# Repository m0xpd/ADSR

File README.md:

# ADSR
A Looping Version of the YuSynth ADSR

# Background

I decided to build a new envelope generator back in December 2022 to supplement / replace my old AR generators made from [MFOS](http://musicfromouterspace.com/) designs and my 
own ["ADSRduino"](https://github.com/m0xpd/ADSRduino).

I already knew Yves Usson's excellent [YuSynth site](https://yusynth.net/Modular/index_en.html) (having published a Eurorack version of the ['Simple VCA'](https://github.com/m0xpd/YuSynth-VCA-for-Eurorack)), and was interested by a comment on 
[Eddy Bergman's website](https://www.eddybergman.com/2020/03/synthesizer-build-part-24-adsr-with.html) about the YuSynth ADSR.

Eddy said:

> "I can say without any doubt that this design is perfect if you want a good and reliable ADSR to pair with your VCA or to drive a filter. " 

That settled it - I would make a Eurorack version of Yves' 7555-based design. However, having added looping to my ADSRduino, 
I decided that I would also like to include the same looping functionality on the new envelope generator. 

So - here it is. A version of the YuSynth 7555 ADSR in 8HP with looping...

<p width=100%, align="center">
 &nbsp &nbsp &nbsp &nbsp &nbsp &nbsp &nbsp &nbsp 
</p>

# Circuit Details

The schematic is seen below (click for a full-sized version and/or download from the 'images' folder).

You will see that I follow Yves' original schematic pretty closely, apart from the addition of the elements required to realise the 
looping functionality. These are:
* a comparator (IC1B) to detect when the envelope falls below the PN junction drop (over D5)
* a positive edge detector (R24/C4/D6) to get a trigger when the envelope falls below the PN junction drop and
* a one-shot monostable multivibrator (Q5,6 etc), to generate a defined pulse from this trigger, 

which is applied via D7 back to the input stage. If the looping switch (SW2) is set appropriately, this pulse can re-trigger the 
envelope and cause 'looping'.

The old-school transistor one-shot is included because I didn't want to add another IC package (having already 'spent' the last stage 
of IC1 on the comparator task).

Other minor departures from Yves' "words and music" include a reduction in input resistor R6 (I had trouble with the specified 1M) and 
substitution of a 2N7000 for Yves' specified BS170 (I see others have had difficuty sourcing these rarer FETs and the garden-variety 
2N7000 works fine). 

I also chose to use once again the lovely [low-profile push button](https://www.thonk.co.uk/shop/low-profile-led-buttons/) as both 
manual gate switch and indicator. It is the right height to work with [Thonkiconns](https://www.thonk.co.uk/shop/thonkiconn/) and [Alpha pots](https://www.thonk.co.uk/shop/alpha-9mm-pots-vertical-t18/), which makes mechanical assembly a breeze.

# Construction Details

Full details of the PCB are given in the [PCB folder](PCB), which includes a .sch and .brd file, developed in EAGLE.

A front panel is decribed by a Kicad project in the [Front Panel folder.](Front%20Panel)

My original boards and Front panel (seen in the images above) were made by JLC, who did their usual competent job. 

The images show the v0.1 boards, which include a Molex KK connector for power which is not on the present V2.0 design. They also have 
different silkscreening, influencing most significantly the licensing...

# Licensing

Yves is clear on the position with copyright on his website:

> "All circuits, schematics, printed circuit board, panel design and associated data published on (yusynth.net) can be used for private use only." 

and:

> "The projects of (yusynth.net) may be build for personal, private usage or educative purpose. Commercial exploitation of the schematics, circuits, 
front panels and software shown on (yusynth.net), is not permitted without a formal agreement with (Yves Usson)".

Accordingly, **the copyright for the core of this ADSR circuit rests with Yves and no commercial exploitation is permitted**.

I have reflected this in the [License](LICENSE.txt) for the looping Eurorack version presented in this repository.

This work is licensed under a
[Creative Commons Attribution-NonCommercial-ShareAlike 4.0 International License.](https://creativecommons.org/licenses/by-nc-sa/4.0/deed.en)

# Specifications

The looping ADSR is 8HP wide and extends 25mm behind the front panel.

It consumes:

7.1mA from the 12V rail (max current in looping mode; quiescent current drain is 3.7mA)  

1.1mA from the -12V rail (in all conditions) 

nothing from the 5V rail.

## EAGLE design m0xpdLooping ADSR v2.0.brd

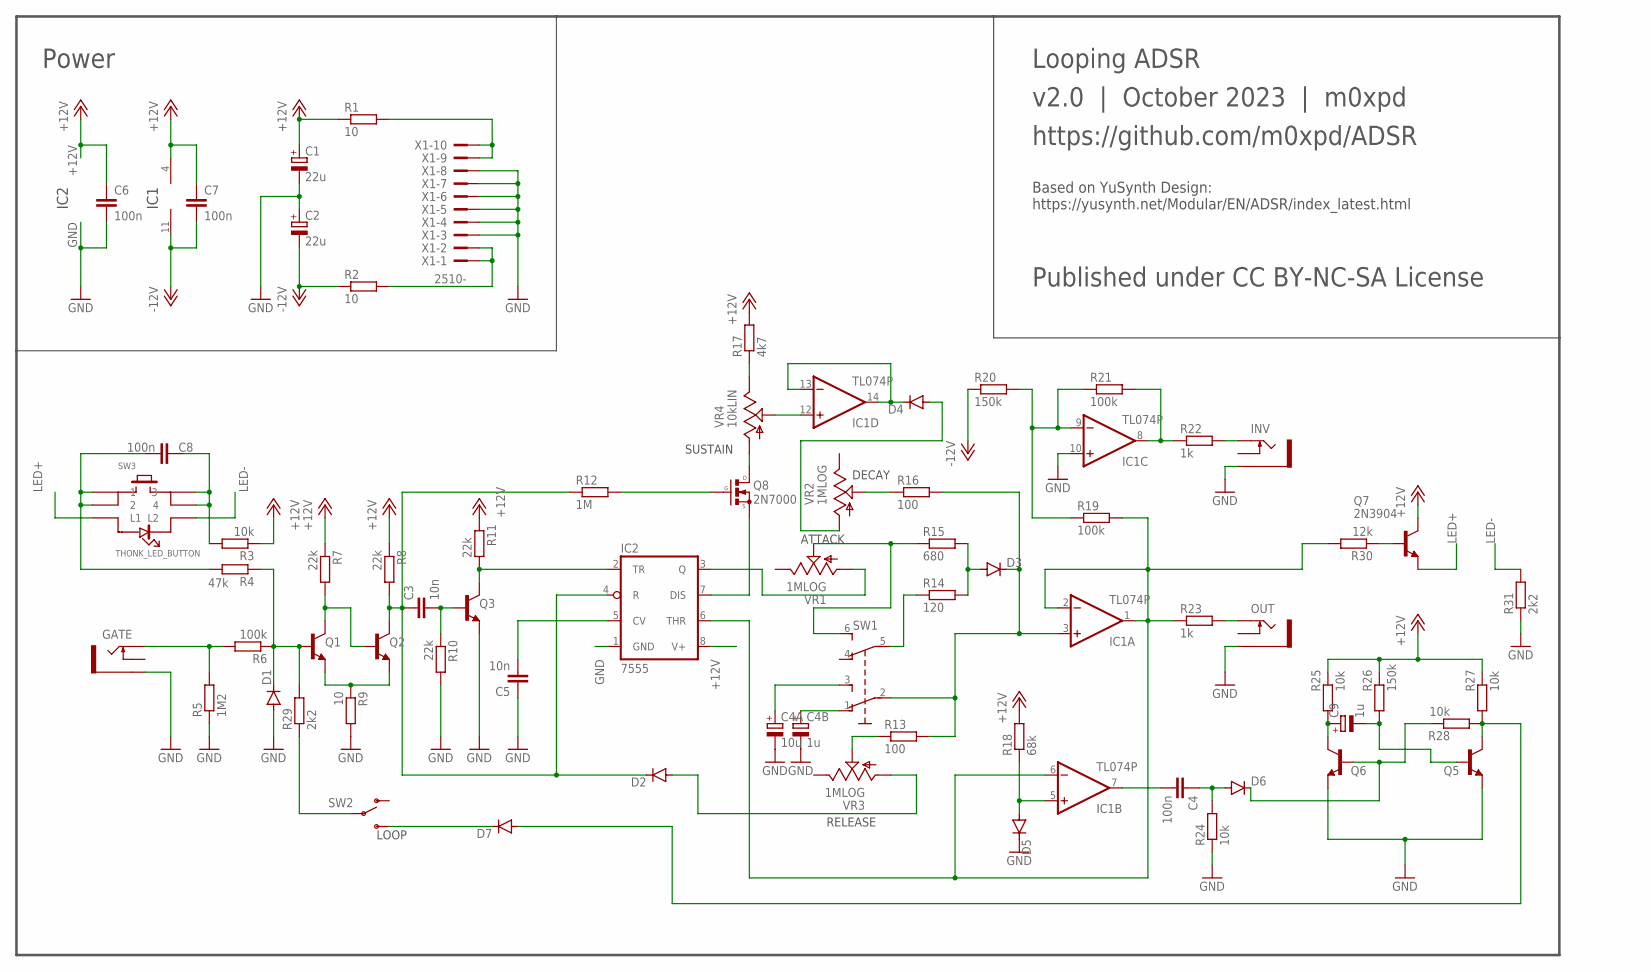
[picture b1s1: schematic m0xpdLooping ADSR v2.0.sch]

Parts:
C1, C2: 22u; E2,5-5
C3, C5: 10n; C050-025X075
C4, C6, C7: 100n; C050-025X075
C4A: 10u; E2,5-5
C4B, C9: 1u; E2,5-5
C8: 100n; C025-030X050
D1, D2, D3, D4, D5, D6, D7: 1N4148DO35-7; DO35-7
GATE: THONKICONNNEW; WQP-PJ301M-12_JACK
IC1: TL074P; DIL14
IC2: 7555; DIL08
INV: THONKICONNNEW; WQP-PJ301M-12_JACK
OUT: THONKICONNNEW; WQP-PJ301M-12_JACK
Q1, Q2, Q3, Q5, Q6, Q7: 2N3904; TO92
Q8: 2N7000; TO92
R1, R2, R9: 10; 0204/7
R3, R24, R25, R27, R28: 10k; 0204/7
R4: 47k; 0204/7
R5: 1M2; 0204/7
R6, R19, R21: 100k; 0204/7
R7, R8, R10, R11: 22k; 0204/7
R12: 1M; 0204/7
R13, R16: 100; 0204/7
R14: 120; 0204/7
R15: 680; 0204/7
R17: 4k7; 0204/7
R18: 68k; 0204/7
R20, R26: 150k; 0204/7
R22, R23: 1k; 0204/7
R29, R31: 2k2; 0204/7
R30: 12k; 0204/7
SW1: TL46PO; TL4XPO
SW2: SUBMINI_SPDT; SUBMINI_TOGGLE
SW3: THONK_LED_BUTTON; LOW_PROFILE_BUTTON
VR1, VR2, VR3: 1MLOG; 9MM_SNAP-IN_POT
VR4: 10kLIN; 9MM_SNAP-IN_POT
X1: 2510-; PAK100/2500-10

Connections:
+12V: C1.+, C6.1, C7.1, IC1.4 (V+), IC2.8 (V+), Q7.1 (C), R1.1, R3.1, R7.1, R8.1, R11.1, R17.2, R18.2, R25.2, R26.2, R27.2
-12V: C2.-, C7.2, IC1.11 (V-), R2.1, R20.1
GND: C1.-, C2.+, C4A.-, C4B.-, C5.1, C6.2, D1.A, D5.C, GATE.P$3_SLEEVE (SLEEVE), IC1.10 (+IN), IC2.1 (GND), INV.P$3_SLEEVE (SLEEVE), OUT.P$3_SLEEVE (SLEEVE), Q3.3 (E), Q5.3 (E), Q6.3 (E), R5.1, R9.2, R10.2, R24.1, R31.1, X1.3, X1.4, X1.5, X1.6, X1.7, X1.8
LED+: Q7.3 (E), SW3.L$1 (L1)
LED-: R31.2, SW3.L$2 (L2)
unnamed: R1.2, X1.9, X1.10
unnamed: GATE.P$1_TIP (TIP), R5.2, R6.2
unnamed: D1.C, Q1.2 (B), R4.1, R6.1, R29.2
unnamed: Q1.3 (E), Q2.3 (E), R9.1
unnamed: R2.2, X1.1, X1.2
unnamed: IC2.3 (Q), VR1.1 (A)
unnamed: Q1.1 (C), Q2.2 (B), R7.2
unnamed: C3.2, Q3.2 (B), R10.1
unnamed: IC2.2 (TR), Q3.1 (C), R11.2
unnamed: C5.2, IC2.5 (CV)
unnamed: C3.1, D2.C, IC2.4 (R), Q2.1 (C), R8.2, R12.1
unnamed: Q8.2 (G), R12.2
unnamed: IC2.7 (DIS), Q8.1 (S)
unnamed: D2.A, VR3.1 (A)
unnamed: Q8.3 (D), VR4.1 (A)
unnamed: R17.1, VR4.3 (E)
unnamed: R13.1, VR3.2 (S)
unnamed: R15.1, SW1.6 (S1), VR1.2 (S)
unnamed: R14.1, SW1.5 (P1)
unnamed: D3.A, R14.2, R15.2
unnamed: D3.C, IC1.3 (+IN), R13.2, R16.2, SW1.2
unnamed: R16.1, VR2.2 (S)
unnamed: C4A.+, SW1.3 (S)
unnamed: C4B.+, SW1.1 (O)
unnamed: IC1.1 (OUT), IC1.2 (-IN), IC1.6 (-IN), IC2.6 (THR), R19.2, R23.1, R30.2
unnamed: IC1.12 (+IN), VR4.2 (S)
unnamed: D4.C, IC1.13 (-IN), IC1.14 (OUT)
unnamed: D4.A, VR2.1 (A)
unnamed: D5.A, IC1.5 (+IN), R18.1
unnamed: IC1.9 (-IN), R19.1, R20.2, R21.1
unnamed: C4.2, IC1.7 (OUT)
unnamed: IC1.8 (OUT), R21.2, R22.1
unnamed: INV.P$1_TIP (TIP), R22.2
unnamed: OUT.P$1_TIP (TIP), R23.2
unnamed: C8.1, R3.2, SW3.P$3 (3), SW3.P$4 (4)
unnamed: C8.2, R4.2, SW3.P$1 (1), SW3.P$2 (2)
unnamed: C4.1, D6.A, R24.2
unnamed: D7.A, Q5.1 (C), R27.1, R28.1
unnamed: C9.+, Q6.1 (C), R25.1
unnamed: R29.1, SW2.COM (COMMON)
unnamed: C9.-, Q5.2 (B), R26.1
unnamed: D7.C, SW2.3 (S)
unnamed: D6.C, Q6.2 (B), R28.2
unnamed: Q7.2 (B), R30.1

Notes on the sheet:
SUSTAIN
DECAY
ATTACK
RELEASE
Looping ADSR
Based on YuSynth Design: https://yusynth.net/Modular/EN/ADSR/index_latest.html
v2.0 | October 2023 | m0xpd
https://github.com/m0xpd/ADSR
Published under CC BY-NC-SA License
LOOP
Power
IC1
IC2

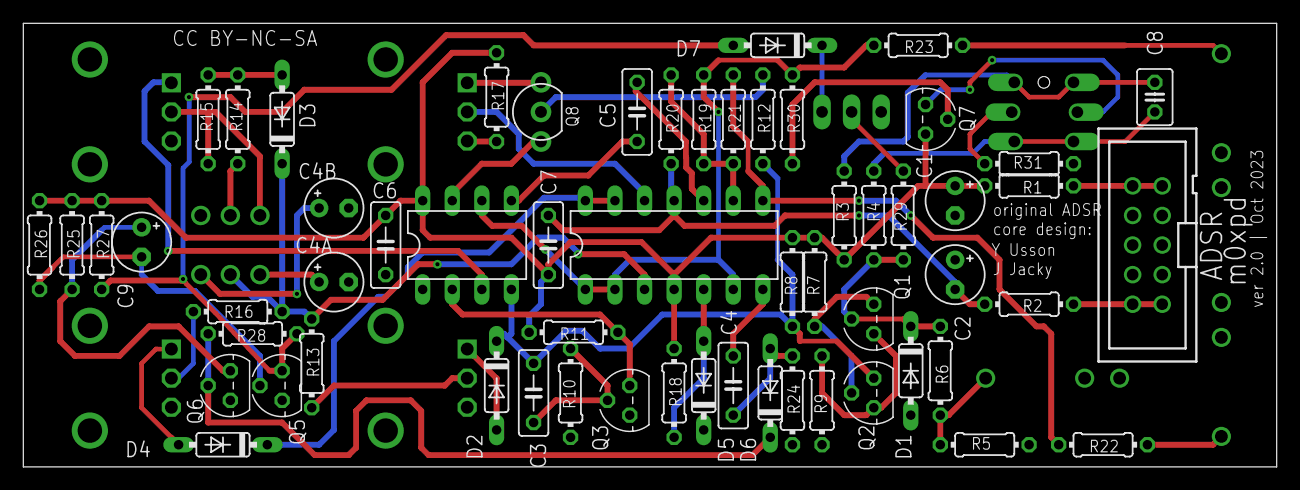
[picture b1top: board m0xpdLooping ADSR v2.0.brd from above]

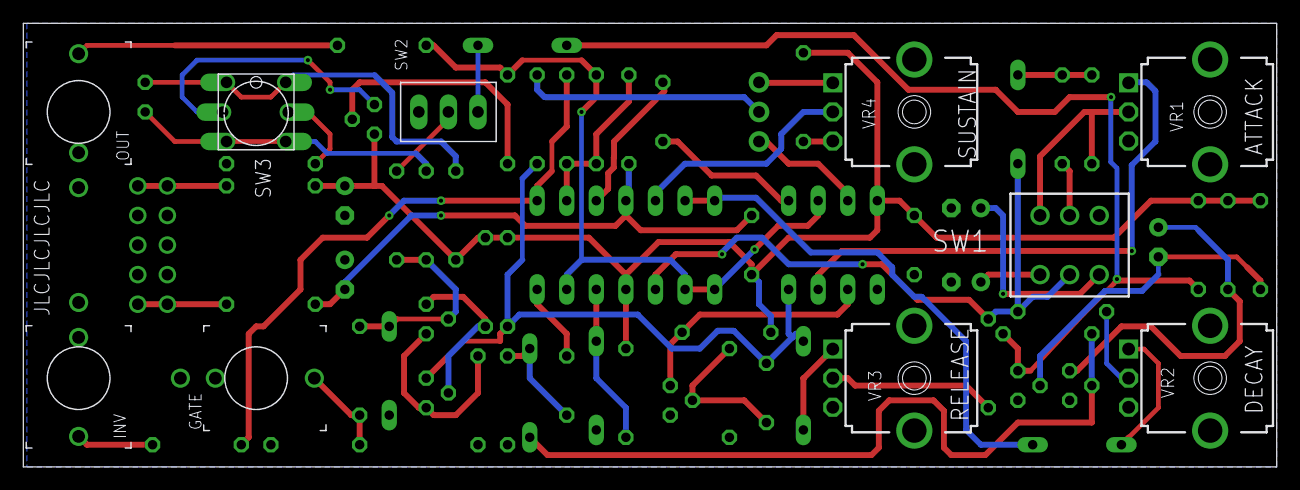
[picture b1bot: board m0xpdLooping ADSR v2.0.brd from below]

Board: 2 copper layers, 107.6 x 38.1 mm, 69 parts (10 on the bottom side), 49 nets.

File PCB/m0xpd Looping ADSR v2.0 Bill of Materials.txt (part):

Partlist exported from /Users/pauldarlington/Documents/EAGLE/projects/555 ADSR/m0xpdLooping ADSR v2.0.sch at 15/10/2023 13:20

Part Value            Device           Package            Description                                                       MF MPN         OC_FARNELL OC_NEWARK POPULARITY SPICEPREFIX
C1   22u              CPOL-EUE2.5-5    E2,5-5             POLARIZED CAPACITOR, European symbol                                                                  16         C          
C2   22u              CPOL-EUE2.5-5    E2,5-5             POLARIZED CAPACITOR, European symbol                                                                  16         C          
C3   10n              C-EU050-025X075  C050-025X075       CAPACITOR, European symbol                                                                            29         C          
C4   100n             C-EU050-025X075  C050-025X075       CAPACITOR, European symbol                                                                            29         C          
C4A  10u              CPOL-EUE2.5-5    E2,5-5             POLARIZED CAPACITOR, European symbol                                                                  16         C          
C4B  1u               CPOL-EUE2.5-5    E2,5-5             POLARIZED CAPACITOR, European symbol                                                                  16         C          
C5   10n              C-EU050-025X075  C050-025X075       CAPACITOR, European symbol                                                                            29         C          
C6   100n             C-EU050-025X075  C050-025X075       CAPACITOR, European symbol                                                                            29         C          
C7   100n             C-EU050-025X075  C050-025X075       CAPACITOR, European symbol                                                                            29         C          
C8   100n             C-EU025-030X050  C025-030X050       CAPACITOR, European symbol                                                                            14         C          
C9   1u               CPOL-EUE2.5-5    E2,5-5             POLARIZED CAPACITOR, European symbol                                                                  16         C          
D1   1N4148DO35-7     1N4148DO35-7     DO35-7             DIODE                                                                                                 58                    
D2   1N4148DO35-7     1N4148DO35-7     DO35-7             DIODE                                                                                                 58                    
D3   1N4148DO35-7     1N4148DO35-7     DO35-7             DIODE                                                                                                 58                    
D4   1N4148DO35-7     1N4148DO35-7     DO35-7             DIODE                                                                                                 58                    
D5   1N4148DO35-7     1N4148DO35-7     DO35-7             DIODE                                                                                                 58                    
D6   1N4148DO35-7     1N4148DO35-7     DO35-7             DIODE                                                                                                 58                    
D7   1N4148DO35-7     1N4148DO35-7     DO35-7             DIODE                                                                                                 58                    
GATE THONKICONNNEW    THONKICONNNEW    WQP-PJ301M-12_JACK 3.5mm socket for Eurorack modular synths                                                                                    
IC1  TL074P           TL074P           DIL14              OP AMP                                                                                                0                     
IC2  7555             7555             DIL08              CMOS 555 timer                                                                                                              
INV  THONKICONNNEW    THONKICONNNEW    WQP-PJ301M-12_JACK 3.5mm socket for Eurorack modular synths                                                                                    
OUT  THONKICONNNEW    THONKICONNNEW    WQP-PJ301M-12_JACK 3.5mm socket for Eurorack modular synths                                                                                    
Q1   2N3904           2N3904           TO92               NPN Transistor                                                                                        0                     
Q2   2N3904           2N3904           TO92               NPN Transistor                                                                                        0                     
Q3   2N3904           2N3904           TO92               NPN Transistor                                                                                        0                     
Q5   2N3904           2N3904           TO92               NPN Transistor                                                                                        0                     
Q6   2N3904           2N3904           TO92               NPN Transistor                                                                                        0                     
Q7   2N3904           2N3904           TO92               NPN Transistor                                                                                        0                     
Q8   2N7000           2N7000           TO92               N-Channel Mosfet                                                                                                            
R1   10               R-EU_0204/7      0204/7             RESISTOR, European symbol                                                                             79         R          
R2   10               R-EU_0204/7      0204/7             RESISTOR, European symbol                                                                             79         R          
R3   10k              R-EU_0204/7      0204/7             RESISTOR, European symbol                                                                             79         R          
R4   47k              R-EU_0204/7      0204/7             RESISTOR, European symbol                                                                             79         R          
R5   1M2              R-EU_0204/7      0204/7             RESISTOR, European symbol                                                                             79         R          
R6   100k             R-EU_0204/7      0204/7             RESISTOR, European symbol                                                                             79         R          
R7   22k              R-EU_0204/7      0204/7             RESISTOR, European symbol                                                                             79         R          
R8   22k              R-EU_0204/7      0204/7             RESISTOR, European symbol                                                                             79         R          
R9   10               R-EU_0204/7      0204/7             RESISTOR, European symbol                                                                             79         R          
R10  22k              R-EU_0204/7      0204/7             RESISTOR, European symbol                                                                             79         R          
R11  22k              R-EU_0204/7      0204/7             RESISTOR, European symbol                                                                             79         R          
R12  1M               R-EU_0204/7      0204/7             RESISTOR, European symbol                                                                             79         R          
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
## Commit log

2023-10-15 Rename Looping ADSR.kicad_pcb to Front Panel/Looping ADSR.kicad_pcb
2023-10-15 Rename Looping ADSR.kicad_pro to Front Panel/Looping ADSR.kicad_pro
2023-10-15 Rename Looping ADSR.kicad_sch to Front Panel/Looping ADSR.kicad_sch
2023-10-15 Rename m0xpdLooping ADSR v2.0.brd to PCB/m0xpdLooping ADSR v2.0.brd
2023-10-15 Rename m0xpdLooping ADSR v2.0.sch to PCB/m0xpdLooping ADSR v2.0.sch
2024-02-08 Rename Front Panel/Looping ADSR.kicad_pcb to Front Panel/OldFiles/Looping ADSR.kicad_pcb
2024-02-08 Rename Front Panel/Looping ADSR.kicad_pro to Front Panel/OldFiles/Looping ADSR.kicad_pro
2024-02-08 Rename Front Panel/Looping ADSR.kicad_sch to Front Panel/OldFiles/Looping ADSR.kicad_sch

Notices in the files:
README.md:
Licensing:
Images/by-nc-sa.eu.png
